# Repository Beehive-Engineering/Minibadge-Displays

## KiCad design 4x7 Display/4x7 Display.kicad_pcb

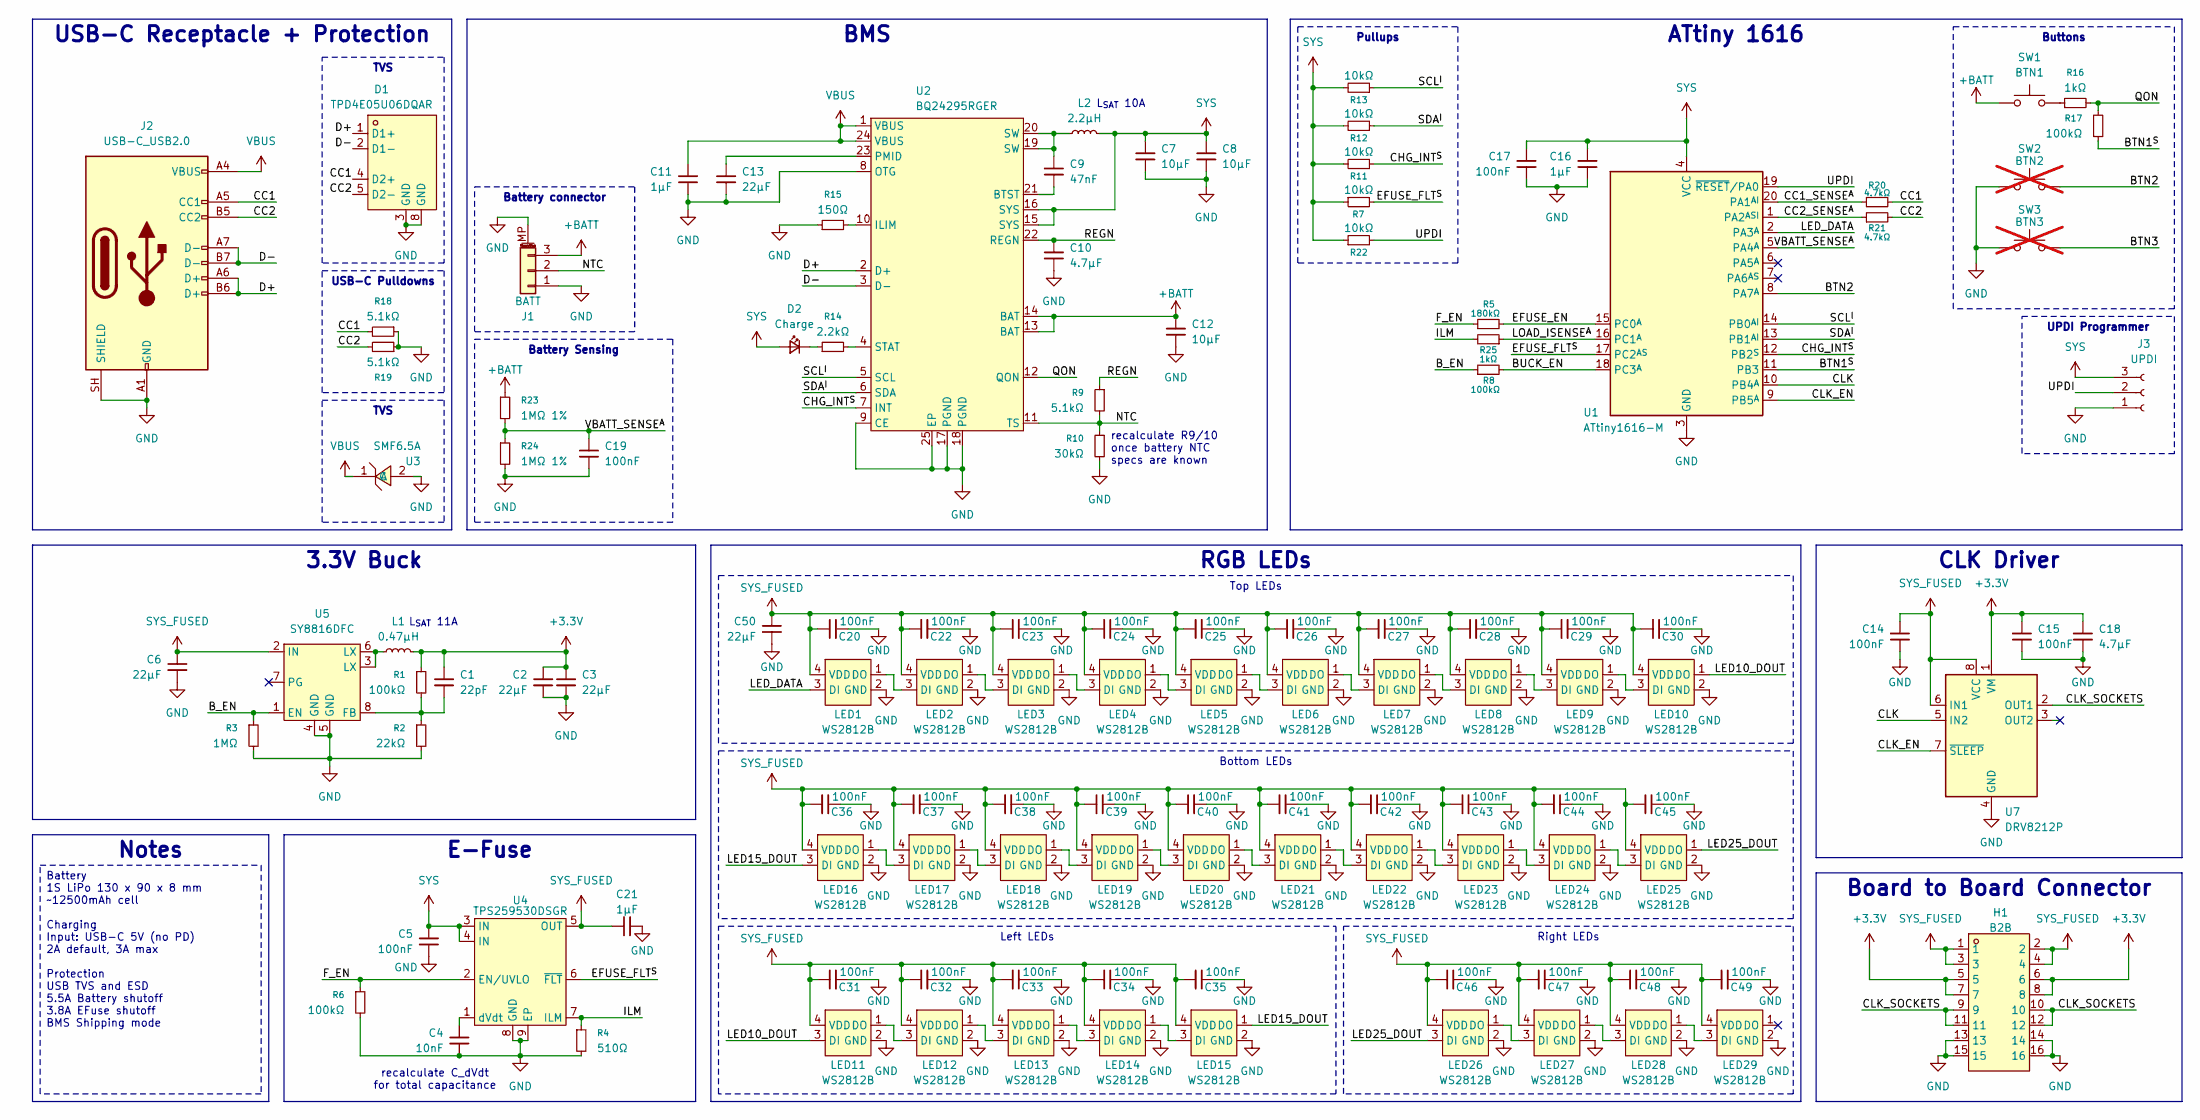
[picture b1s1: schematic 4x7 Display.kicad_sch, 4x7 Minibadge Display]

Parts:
C1: 22pF; C_0603_1608Metric; LCSC Part # C1653
C2, C3, C6, C13, C50: 22μF; C_1206_3216Metric; LCSC Part # C12891
C4: 10nF; C_0603_1608Metric; LCSC Part # C57112
C5, C14, C15, C17, C19, C20, C22, C23, C24, C25, C26, C27, C28, C29, C30, C31, C32, C33, C34, C35, C36, C37, C38, C39, C40, C41, C42, C43, C44, C45, C46, C47, C48, C49: 100nF; C_0603_1608Metric; LCSC Part # C14663
C7, C8, C12: 10μF; C_1206_3216Metric; LCSC Part # C13585
C9: 47nF; C_0603_1608Metric; LCSC Part # C1622
C10, C18: 4.7μF; C_1206_3216Metric; LCSC Part # C29823
C11, C16, C21: 1μF; C_0603_1608Metric; LCSC Part # C15849
D1: TPD4E05U06DQAR; USON-10_L2.5-W1.0-P0.50-BL; MPN TPD4E05U06DQAR; LCSC Part C138714
D2: Charge; D_0603_1608Metric; LCSC Part # C2286
H1: B2B; HDR-SMD_16P-P2.54-V-F-R2-C8-LS7.1; MPN PM254-2-08-S-8.5; LCSC Part C3975153
J1: BATT; JST_XH_S3B-XH-SM4-TB_1x03-1MP_P2.50mm_Horizontal
J2: USB-C_USB2.0; USB_C_Receptacle_HRO_TYPE-C-31-M-12; LCSC Part # C165948
J3: UPDI; PinHeader_1x03_P2.54mm_Vertical
L1: 0.47μH; IND-SMD_L5.4-W5.2_FXL0530
L2: 2.2μH; IND-SMD_L7.0-W6.6; LCSC Part # C167218
LED1, LED2, LED3, LED4, LED5, LED6, LED7, LED8, LED9, LED10, LED11, LED12, LED13, LED14, LED15, LED16, LED17, LED18, LED19, LED20, LED21, LED22, LED23, LED24, LED25, LED26, LED27, LED28, LED29: WS2812B; LED-SMD_4P-L2.2-W2.0-P1.00_WS2815C-2020-4P; MPN WS2812B-2020-V6; LCSC Part C52917434
R1, R6, R8, R17: 100kΩ; R_0603_1608Metric; LCSC Part # C25803
R2: 22kΩ; R_0603_1608Metric; LCSC Part # C31850
R3: 1MΩ; R_0603_1608Metric; LCSC Part # C22935
R4: 510Ω; R_0603_1608Metric; LCSC Part # C23193
R5: 180kΩ; R_0603_1608Metric; LCSC Part # C22827
R7, R11, R12, R13, R22: 10kΩ; R_0603_1608Metric; LCSC Part # C25804
R9, R18, R19: 5.1kΩ; R_0603_1608Metric; LCSC Part # C23186
R10: 30kΩ; R_0603_1608Metric; LCSC Part # C22984
R14: 2.2kΩ; R_0603_1608Metric; LCSC Part # C4190
R15: 150Ω; R_0603_1608Metric; LCSC Part # C22808
R16, R25: 1kΩ; R_0603_1608Metric; LCSC Part # C21190
R20, R21: 4.7kΩ; R_0603_1608Metric; LCSC Part # C23162
R23, R24: 1MΩ 1%; R_0603_1608Metric; LCSC Part # C22935
SW1: BTN1; SW_Tactile_SPST_Angled_PTS645Vx83-2LFS; LCSC Part # C127486
SW2: BTN2; SW_Tactile_SPST_Angled_PTS645Vx83-2LFS; LCSC Part # C125034; not fitted
SW3: BTN3; SW_Tactile_SPST_Angled_PTS645Vx83-2LFS; LCSC Part # C125034; not fitted
U1: ATtiny1616-M; VQFN-20-1EP_3x3mm_P0.4mm_EP1.7x1.7mm; LCSC Part # C507118
U2: BQ24295RGER; VQFN-24-1EP_4x4mm_P0.5mm_EP2.5x2.5mm_ThermalVias; MPN BQ24295RGER; LCSC Part C165144
U3: SMF6.5A; SOD-123FL_L2.8-W1.8-LS3.8-RD; MPN SMF6.5A; LCSC Part C5370410
U4: TPS259530DSGR; WSON-8_L2.0-W2.0-P0.50-TL-EP; MPN TPS259530DSGR; LCSC Part C2155775
U5: SY8816DFC; DFN-8_L2.0-W2.0_SY8816DFC; MPN SY8816DFC; LCSC Part C5440878
U7: DRV8212P; Texas_DSG0008A_WSON-8-1EP_2x2mm_P0.5mm_EP0.9x1.6mm_ThermalV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; LCSC Part # C5208051

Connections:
+3.3V: C1.1, C2.1, C3.1, C15.1, C18.1, H1.5, H1.6, H1.7, H1.8, L1.2, R1.1, U7.1 (VM)
+BATT: C12.1, J1.3, R23.1, SW1.1, U2.13 (BAT), U2.14 (BAT)
/BTN1^{S}: R17.1, U1.11 (PB3)
/BTN2: SW2.1, U1.8 (PA7^{A})
/BUCK_EN: R8.2, U1.18 (PC3^{A})
/B_EN: R3.1, R8.1, U5.1 (EN)
/CC1: D1.4 (D2+), J2.A5 (CC1), R18.2, R20.2
/CC1_SENSE^{A}: R20.1, U1.20 (PA1^{AI})
/CC2: D1.5 (D2-), J2.B5 (CC2), R19.2, R21.2
/CC2_SENSE^{A}: R21.1, U1.1 (PA2^{ASI})
/CHG_INT^{S}: R11.1, U1.12 (PB2^{S}), U2.7 (INT)
/CLK: U1.10 (PB4^{A}), U7.5 (IN2)
/CLK_EN: U1.9 (PB5^{A}), U7.7 (~SLEEP)
/CLK_SOCKETS: H1.9, H1.10, H1.11, H1.12, U7.2 (OUT1)
/D+: D1.1 (D1+), J2.A6 (D+), J2.B6 (D+), U2.2 (D+)
/D-: D1.2 (D1-), J2.A7 (D-), J2.B7 (D-), U2.3 (D-)
/EFUSE_EN: R5.2, U1.15 (PC0^{A})
/EFUSE_FLT^{S}: R7.2, U1.17 (PC2^{AS}), U4.6 (~FLT)
/F_EN: R5.1, R6.1, U4.2 (EN/UVLO)
/ILM: R4.1, R25.2, U4.7 (ILM)
/LED10_DOUT: LED10.1 (DO), LED11.3 (DI)
/LED15_DOUT: LED15.1 (DO), LED16.3 (DI)
/LED25_DOUT: LED25.1 (DO), LED26.3 (DI)
/LED_DATA: LED1.3 (DI), U1.2 (PA3^{A})
/LOAD_ISENSE^{A}: R25.1, U1.16 (PC1^{A})
/NTC: J1.2, R9.2, R10.1, U2.11 (TS)
/QON: R16.2, R17.2, U2.12 (QON)
/REGN: C10.1, R9.1, U2.22 (REGN)
/SCL^{I}: R13.1, U1.14 (PB0^{AI}), U2.5 (SCL)
/SDA^{I}: R12.1, U1.13 (PB1^{AI}), U2.6 (SDA)
/UPDI: J3.2, R22.2, U1.19 (~RESET/PA0)
/VBATT_SENSE^{A}: C19.1, R23.2, R24.1, U1.5 (PA4^{A})
GND: C2.2, C3.2, C4.2, C5.2, C6.2, C7.2, C8.2, C10.2, C11.2, C12.2, C13.1, C14.2, C15.2, C16.2, C17.2, C18.2, C19.2, C20.2, C21.2, C22.2, C23.2, C24.2, C25.2, C26.2, C27.2, C28.2, C29.2, C30.2, C31.2, C32.2, C33.2, C34.2, C35.2, C36.2, C37.2, C38.2, C39.2, C40.2, C41.2, C42.2, C43.2, C44.2, C45.2, C46.2, C47.2, C48.2, C49.2, C50.2, D1.3 (GND), D1.8 (GND), H1.13, H1.14, H1.15, H1.16, J1.1, J1.MP (MountPin), J2.A1 (GND), J2.A12 (GND), J2.B1 (GND), J2.B12 (GND), J2.SH (SHIELD), J3.1, LED1.2 (GND), LED2.2 (GND), LED3.2 (GND), LED4.2 (GND), LED5.2 (GND), LED6.2 (GND), LED7.2 (GND), LED8.2 (GND), LED9.2 (GND), LED10.2 (GND), LED11.2 (GND), LED12.2 (GND), LED13.2 (GND), LED14.2 (GND), LED15.2 (GND), LED16.2 (GND), LED17.2 (GND), LED18.2 (GND), LED19.2 (GND), LED20.2 (GND), LED21.2 (GND), LED22.2 (GND), LED23.2 (GND), LED24.2 (GND), LED25.2 (GND), LED26.2 (GND), LED27.2 (GND), LED28.2 (GND), LED29.2 (GND), R2.2, R3.2, R4.2, R6.2, R10.2, R15.1, R18.1, R19.1, R24.2, SW2.2, SW3.2, U1.3 (GND), U1.21 (GND), U2.8 (OTG), U2.9 (CE), U2.17 (PGND), U2.18 (PGND), U2.25 (EP), U3.2 (A), U4.8 (GND), U4.9 (EP), U5.4 (GND), U5.5 (GND), U7.4 (GND), U7.9 (GND)
unnamed: C9.1, L2.1, U2.19 (SW), U2.20 (SW)
unnamed: D2.1 (K), R14.1
unnamed: L1.1, U5.3 (LX), U5.6 (LX)
unnamed: LED1.1 (DO), LED2.3 (DI)
unnamed: LED2.1 (DO), LED3.3 (DI)
unnamed: LED3.1 (DO), LED4.3 (DI)
unnamed: LED4.1 (DO), LED5.3 (DI)
unnamed: LED5.1 (DO), LED6.3 (DI)
unnamed: LED6.1 (DO), LED7.3 (DI)
unnamed: LED7.1 (DO), LED8.3 (DI)
unnamed: LED8.1 (DO), LED9.3 (DI)
unnamed: LED9.1 (DO), LED10.3 (DI)
unnamed: LED11.1 (DO), LED12.3 (DI)
unnamed: LED12.1 (DO), LED13.3 (DI)
unnamed: LED13.1 (DO), LED14.3 (DI)
unnamed: LED14.1 (DO), LED15.3 (DI)
unnamed: LED16.1 (DO), LED17.3 (DI)
unnamed: LED17.1 (DO), LED18.3 (DI)
unnamed: LED18.1 (DO), LED19.3 (DI)
unnamed: LED19.1 (DO), LED20.3 (DI)
unnamed: LED20.1 (DO), LED21.3 (DI)
unnamed: LED21.1 (DO), LED22.3 (DI)
unnamed: LED22.1 (DO), LED23.3 (DI)
unnamed: LED23.1 (DO), LED24.3 (DI)
unnamed: LED24.1 (DO), LED25.3 (DI)
unnamed: LED26.1 (DO), LED27.3 (DI)
unnamed: LED27.1 (DO), LED28.3 (DI)
unnamed: LED28.1 (DO), LED29.3 (DI)
unnamed: R16.1, SW1.2
unnamed: C9.2, U2.21 (BTST)
unnamed: R15.2, U2.10 (ILIM)
unnamed: C13.2, U2.23 (PMID)
unnamed: R14.2, U2.4 (STAT)
unnamed: C4.1, U4.1 (dVdt)
unnamed: C1.2, R1.2, R2.1, U5.8 (FB)
SYS: C5.1, C7.1, C8.1, C16.1, C17.1, D2.2 (A), J3.3, L2.2, R7.1, R11.2, R12.2, R13.2, R22.1, U1.4 (VCC), U2.15 (SYS), U2.16 (SYS), U4.3 (IN), U4.4 (IN)
SYS_FUSED: C6.1, C14.1, C20.1, C21.1, C22.1, C23.1, C24.1, C25.1, C26.1, C27.1, C28.1, C29.1, C30.1, C31.1, C32.1, C33.1, C34.1, C35.1, C36.1, C37.1, C38.1, C39.1, C40.1, C41.1, C42.1, C43.1, C44.1, C45.1, C46.1, C47.1, C48.1, C49.1, C50.1, H1.1, H1.2, H1.3, H1.4, LED1.4 (VDD), LED2.4 (VDD), LED3.4 (VDD), LED4.4 (VDD), LED5.4 (VDD), LED6.4 (VDD), LED7.4 (VDD), LED8.4 (VDD), LED9.4 (VDD), LED10.4 (VDD), LED11.4 (VDD), LED12.4 (VDD), LED13.4 (VDD), LED14.4 (VDD), LED15.4 (VDD), LED16.4 (VDD), LED17.4 (VDD), LED18.4 (VDD), LED19.4 (VDD), LED20.4 (VDD), LED21.4 (VDD), LED22.4 (VDD), LED23.4 (VDD), LED24.4 (VDD), LED25.4 (VDD), LED26.4 (VDD), LED27.4 (VDD), LED28.4 (VDD), LED29.4 (VDD), U4.5 (OUT), U5.2 (IN), U7.6 (IN1), U7.8 (VCC)
VBUS: C11.1, J2.A4 (VBUS), J2.A9 (VBUS), J2.B4 (VBUS), J2.B9 (VBUS), U2.1 (VBUS), U2.24 (VBUS), U3.1 (C)

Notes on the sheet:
L_{SAT} 10A
recalculate R9/10 once battery NTC specs are known
L_{SAT} 11A
recalculate C_dVdt for total capacitance
CLK Driver
Battery Sensing
USB-C Receptacle + Protection
TVS
Battery connector
Right LEDs
Battery 1S LiPo 130 x 90 x 8 mm ~12500mAh cell Charging Input: USB-C 5V (no PD) 2A default, 3A max Protection USB TVS and ESD 5.5A Battery shutoff 3.8A EFuse shutoff BMS Shipping mode
3.3V Buck
USB-C Pulldowns
Notes
Left LEDs
Pullups
ATtiny 1616
BMS
Buttons
E-Fuse
RGB LEDs
Board to Board Connector
Bottom LEDs
UPDI Programmer
Top LEDs

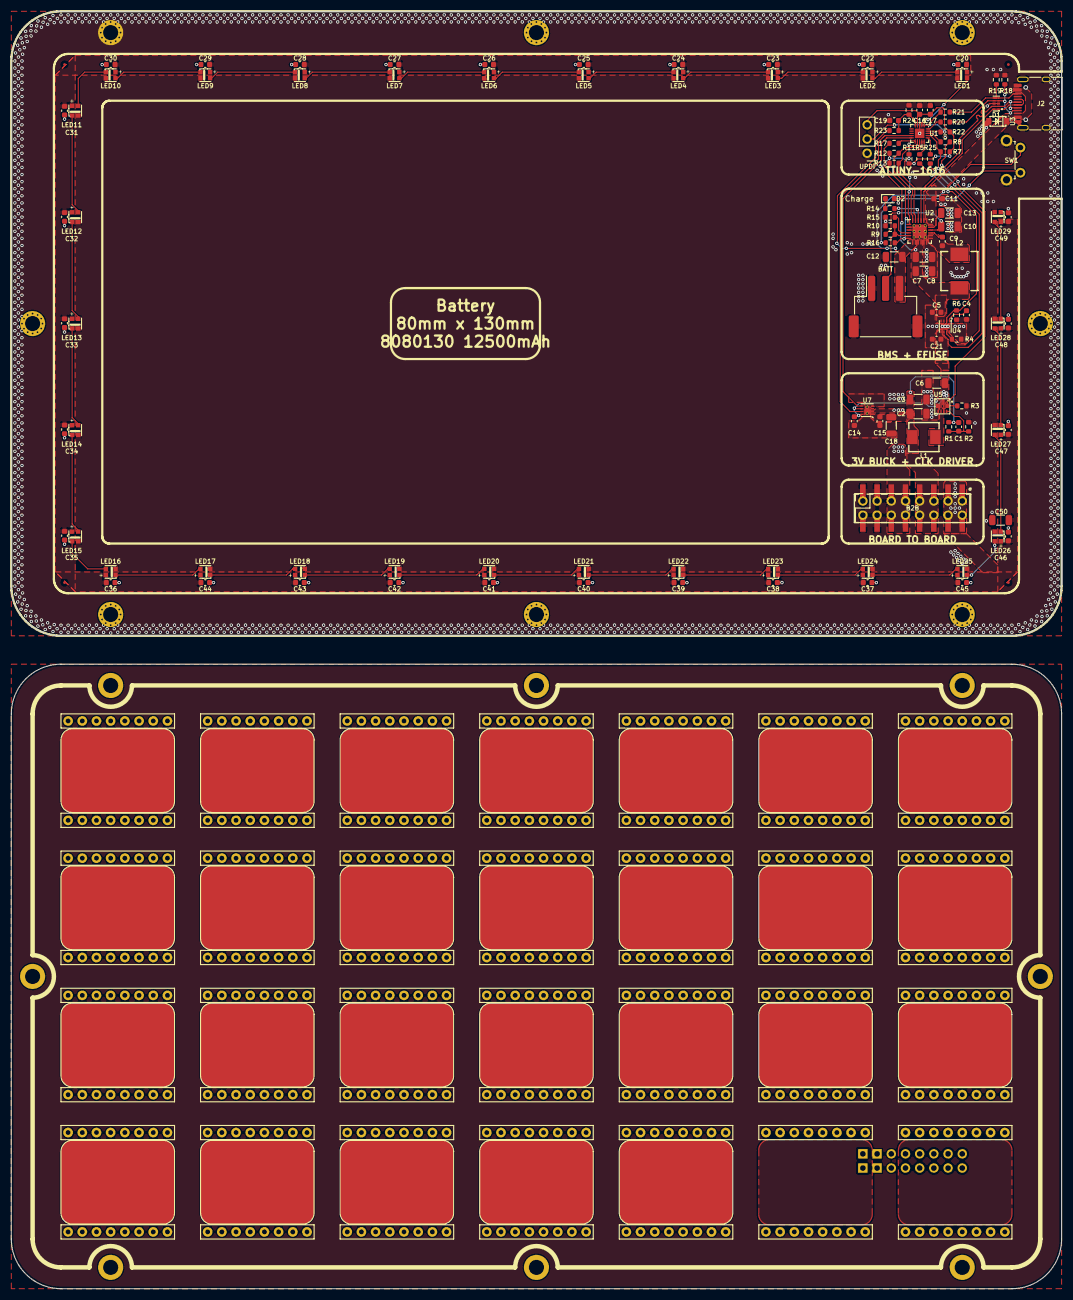
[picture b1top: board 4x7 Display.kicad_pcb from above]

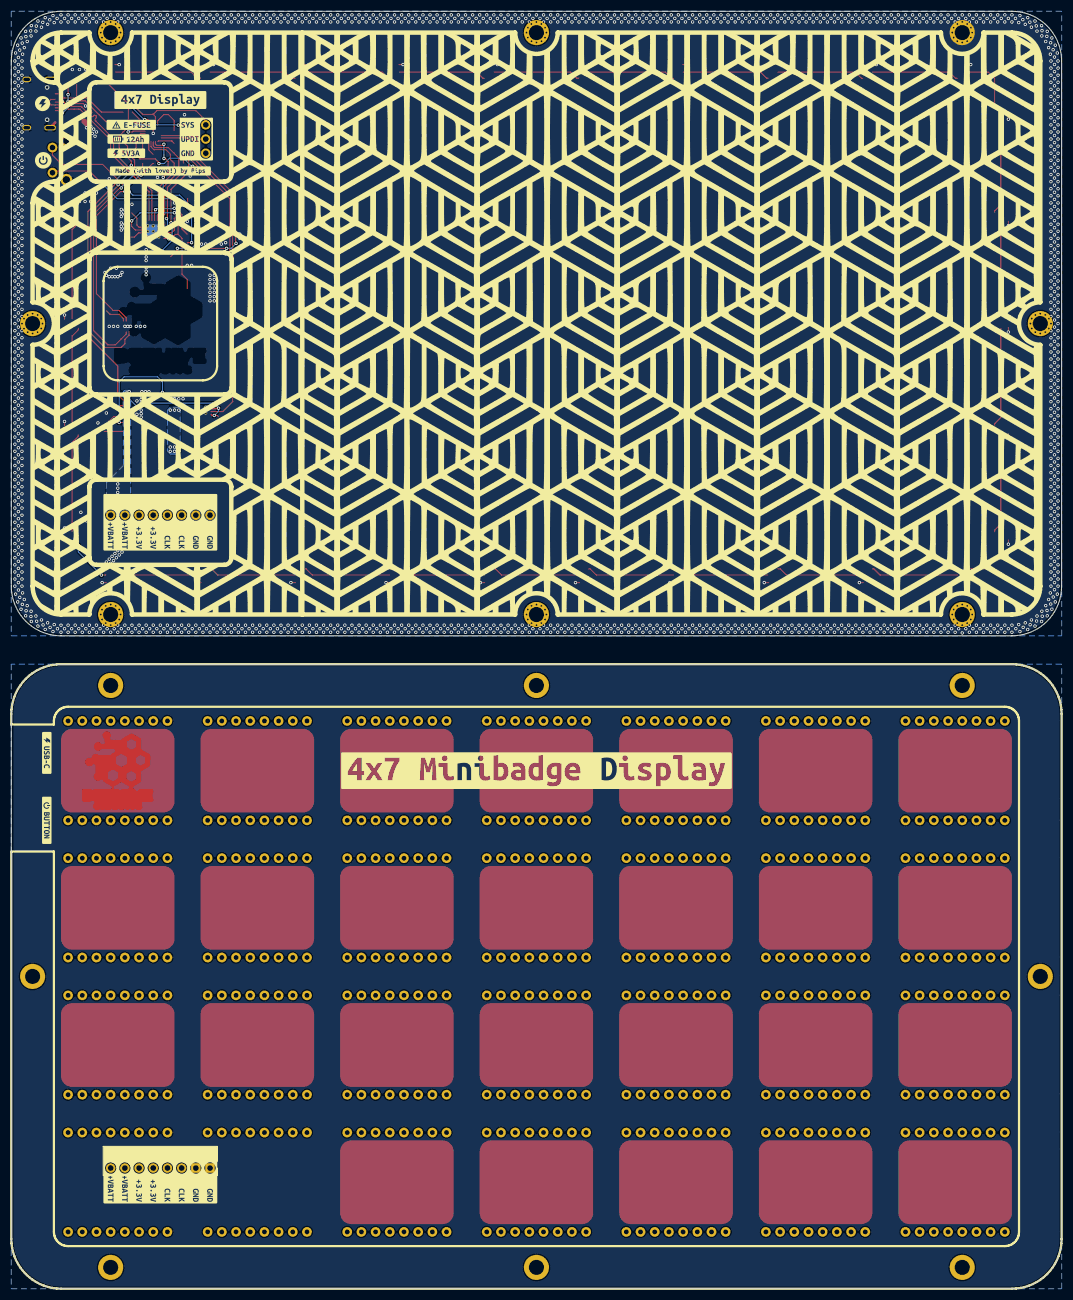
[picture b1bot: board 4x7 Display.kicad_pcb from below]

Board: 2 copper layers, 188.0 x 228.6 mm, 132 parts (13 on the bottom side), 70 nets.

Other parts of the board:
kobee-studio-6AF5A00E, kobee-studio-6AF59FA8, kobee-studio-6AF595D4, kobee-studio-6AF59616, kobee-studio-6AF59873: Kobee Studio; kobee-studio-6AF59280
kobee-studio-6AF6B32B, kobee-studio-6AF6B32B#2: Kobee Studio; kobee-studio-6AF51534
kobee-studio-6AF6C267: Kobee Studio; kobee-studio-6AF6C03E
kobee-studio-6AF59E14: Kobee Studio; kobee-studio-6AF517E5
kobee-studio-6AF62A46, kobee-studio-6AF62AB0: Kobee Studio; kobee-studio-6AF629F5
kobee-studio-6AF63128, kobee-studio-6AF63151: Kobee Studio; kobee-studio-6AF62E07
